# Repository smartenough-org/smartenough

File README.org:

* SmartEnough
SmartEnough is an open source smart home solution that combines affordable
off-the-shelf hardware with a robust software architecture. Built for people
that don't want to pay premium for each IO they add to the system, who want to
trust the system's reliability and who are not afraid of some tinkering.

** SmartEnough design goals
- Extra cheap hardware: doable by hand (soldering iron or breadboard) and
  upgradable to something more sturdy with ordered PCBs. 48+ IO per single board
  possible and way cheaper $/IO than in any available commercial solutions.
- Robust, resiliant, secure: communication and power over twisted pair cables -
  no batteries, no radio, no cloud.
- Supports house wiring in "constellation of star topologies". We don't have a
  device in each light switch or socket, but neither are we limited to a single
  central control point. Cables from lights/shutters and switches should meet
  somewhere in one or more electrical boxes that are connected together with a
  twisted pair cable to form a CAN bus. Bus can span multiple devices in single
  electrical box, or connect multiple points in a bus or semi-bus configuration.
- Instant response to input.
- Event on one board can cause an action on another (eg. stair switches) via a
  bus without requiring a computer and HomeAssistant - eg. stair lighting.
- Can gather door/window/movement sensor data and be used as an alarm system.
- Open & customizable: I'm building it to suit my needs, trying to keep it open
  for any additional sensible functions.
- Integrates with HomeAssistant, but can do a lot without it.

** Resources
The core system software is in two repositories:
- [[https://github.com/smartenough-org/io-ctrl][io-ctrl]]:
  Firmware for IO controller board that handles IO - reads switches and
  sensors, changes outputs. Contains also firmware for hardware part (left side)
  of =CAN<->USB<->MQTT= bridge to talk to HomeAssistant.
- [[https://github.com/smartenough-org/io-gate][io-gate]]:
  computer part of =CAN<->USB<->MQT= bridge (right part) to convert CAN
  messages to MQTT events that can be understood by HomeAssistant.
- Firmware is in Rust, written with Embassy framework for STM32G431 device.
  Should migrate easy enough to other chips assuming enough peripherals are
  available (CAN and USB working together, 128kB+ Flash, 32kB+ RAM).

Rest of the resources include:
- KiCAD (schematic + board) designs for IO controller board (can be used for
  gate as well).
- KiCAD for organized power injection with protection.
- KiCAD for additional ESPHOME boards for less critical components (like
  temperature sensors).
- 3D printing (FreeCad) designs for DIN rail (mount in electrical boxes) and
  other project boxes for boards (OpenSCAD).
- This repository in addition can contain anything smarthome related I might
  publish (eg. some micropython watering experiments)

** Example deployment
[[media/deployment-diagram.png]]

That's my currently working deployment. NOTE: CAN should not be a star, it
should be a bus. Hence in one case I send CAN signal back over another cable
pair in the same cable to "flatten" it out. Bus gets longer (it's around 50m
total), but stubs are shorter.

*** Connecting cables
I use two pairs for power, one for CAN and one for optional CAN return and a bit
weird RJ45 wiring to indicate the cable is a "SMART" cable not Ethernet. I also
mark those in a visible way. Anything will work as long as CAN and FORWARD is in
the same twisted pair (my mapping will work with normal T568B too).

| T568B | CAN  |   |                       |
|-------+------+---+-----------------------|
| w-o   | w-o  | 1 | CAN_L                 |
| o     | o    | 2 | CAN_H                 |
| w-g   | w-g  | 3 | IN POWER, 24V         |
| bl    | g    | 4 | IN POWER, GND (swap!) |
| w-bl  | w-bl | 5 | IN POWER, 24V         |
| g     | bl   | 6 | IN POWER, GND (swap!) |
| w-br  | w-br | 7 | CAN_L FORWARD         |
| br    | br   | 8 | CAN_H FORWARD         |

*** CAN configuration
I use CAN because it's a multi-master bus, no "leader" device on the BUS needs
to poll for data from "following" devices. When input event occurs or output
changes state a board broadcasts a message on the bus. Another board can see
this message and react by changing it's outputs.

Gate is a special device that serves as a bidirectional =CAN<->USB<->MQTT=
bridge. It receives CAN messages, converts them and publishes them on MQTT. It
also subscribes to MQTT topics and if something is published there it sends a
CAN request to for example toggle an Output.

I use 250kbps CAN speed and 11-bit addressing. I opted for a simple CAN protocol
(as opposed to more versatile CANopen). Address relates to a "message" more than
a "sender/receiver" and is used in determining the priority on the bus. Given
that:
- Messages must be properly unique,
- lower values have higher priorities,
- we want at least 64 devices on the bus,
I picked 6 bit for device address and 5 for message type (32 different message
types). Format: =TTTTTAAAAAA (T)ype + (A)ddress=.

Reporting errors, propagating output/input changes, setting output has higher
priority than requesting status, reporting status, time announcements or some
debug ping/pong messages.

Message body consists of up to 8 bytes of data, system typically uses 2-3.
Example: Request output change has 2 bytes: Index of output to change and byte
representing state (Off, On, Toggle). Message address points at the device that
should change output ("destination").

Message "Output changed" has similarly output index and state (Off, On), but
address points to a message source instead. I don't use RTR (remote frames).

Conscise list of used commands (but see message.rs for details):
- ERROR 0x02 - Error happened.
- OUTPUT_CHANGED 0x04 - My output changed
- INPUT_CHANGED 0x05 -  My input was changed
- SET_OUTPUT 0x08 - Set output X to Y (or invert state)
- CALL_PROC 0x0A - Call a predefined procedure in VM
- CALL_SHUTTER 0x0B - Pass command to Shutter code
- STATUS_IO 0x0E - My current IO status, not necessarily changed.
- INFO 0x12 - Similar to ERROR, but low priority (eg. Device started)
- PONG 0x1D
- PING 0x1E

Call Shutter is longest command as it includes a shutter index and a command
byte that can contain a height and a tilt of the shutter.

** IO Controller MainBoard
For details on components and software see
[[https://github.com/smartenough-org/io-ctrl][io-ctrl]].

This board controls IOs when paired with some relay/SSR module. It sits in an
electrical box where it can read signals from light switches and control power
to lighting. It's talks with the world via classical twisted pair cable: CAT5e
UTP. Cable carries power (24V+) and a CAN bus.

[[hardware/board_v1.png]]
[[hardware/schematic_v1.png]]

** Power distribution board
Power board distributes power with some protection (capacitors, resettable
individual fuses, main fuses, zener diodes to limit voltage, diodes to prevent
invalid polarization). It also connects CAN BUS together in configured various
ways (directly, or using FORWARD pair). In general it allows me to connect the
cables from boards in the main central hub easily.

[[hardware/powerboard_v1.png]]

** ESPHome "Uniboard"
It's not strictly part of my main smarthome. A universal PCB board for ESP32 S2
Mini modules I have. It has power stabilization, 1-wire pull-up, some analog
inputs, RS485 interface, four MOSFETs for RGBW or anything else (garage door
control).

I use it with Esphome (over Wifi) where I can't reach with my CAN bus, or where
I don't need the resiliency or just temporarily. For example to gather
temperature readings around heat pump.

[[hardware/uniboard.png]]

** Greenfinger

Automatic plant watering using ESP8266 (or ESP32) using Micropython.
Integrates with HomeAssistant over MQTT:
- Reports status (humidity, operations).
- Can be controlled over MQTT (more water NOW).

It was 100% stable during a period of about a year. Plants died for unrelated
reasons. ;)

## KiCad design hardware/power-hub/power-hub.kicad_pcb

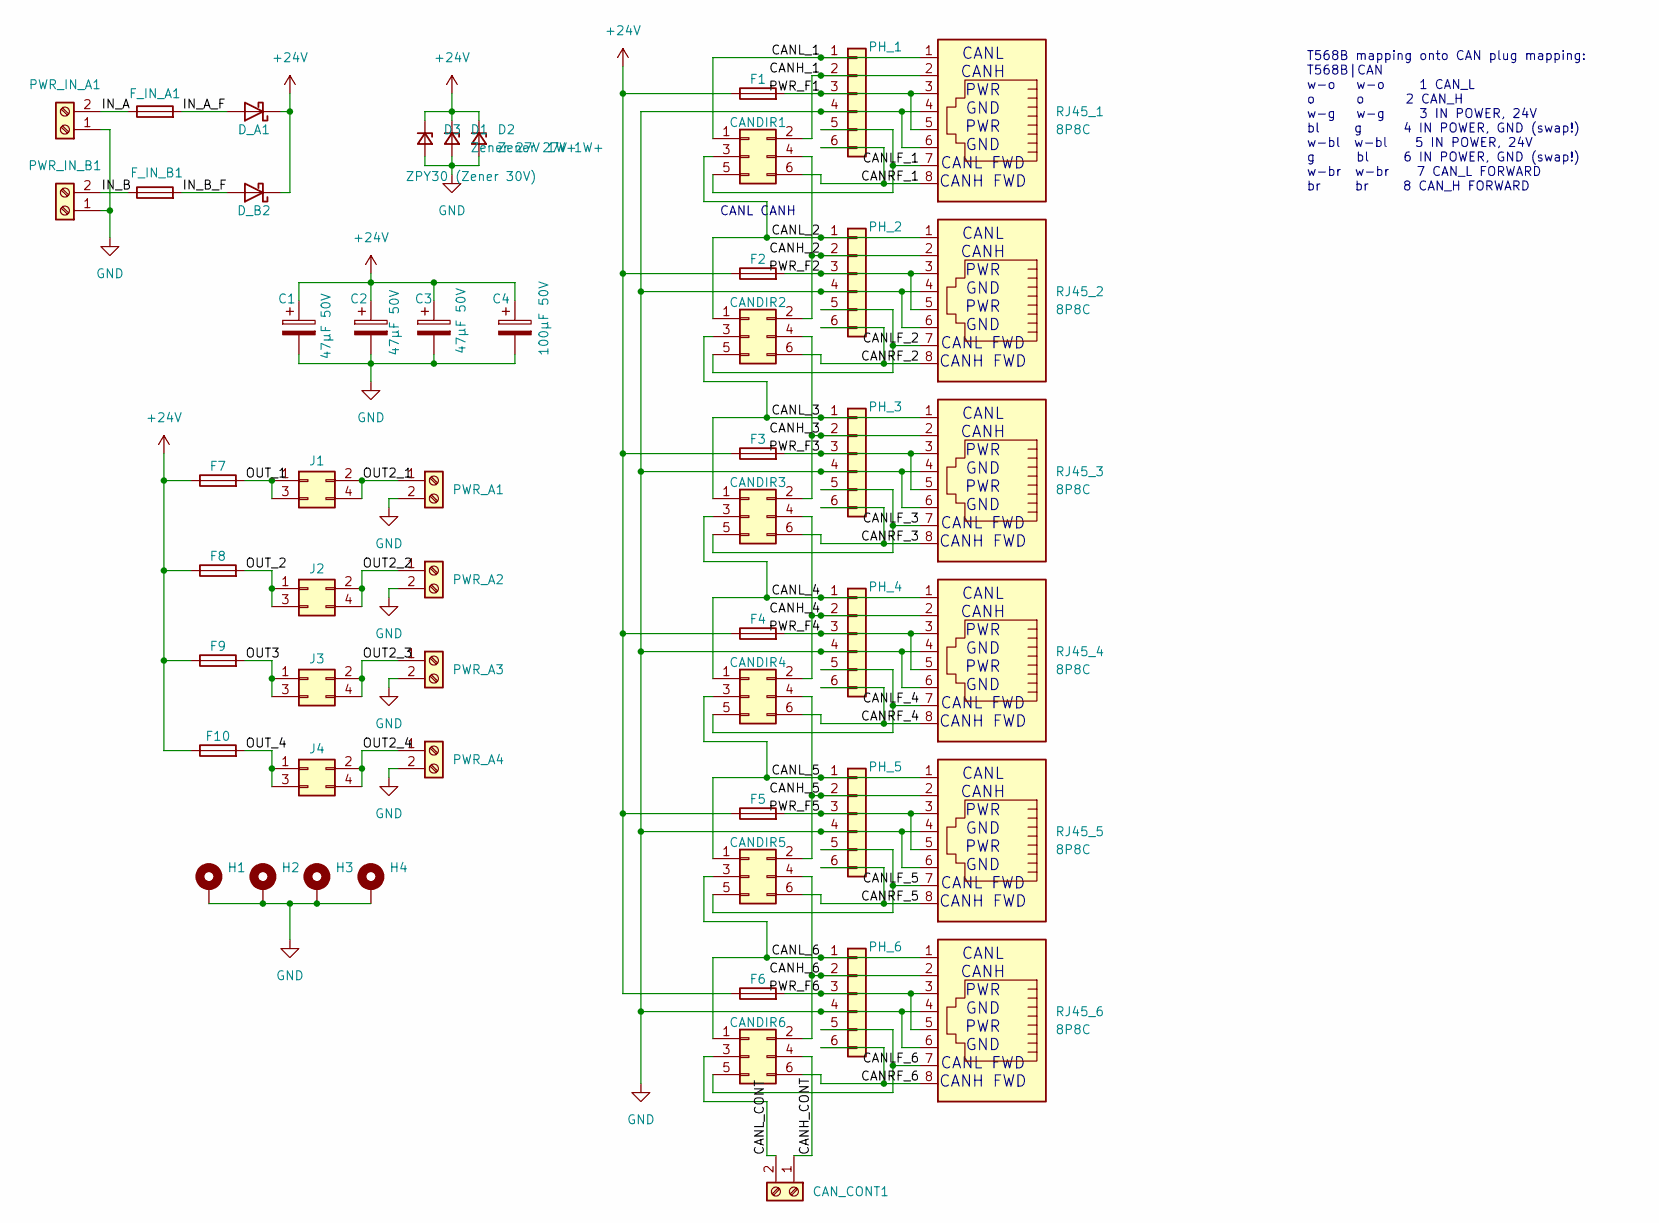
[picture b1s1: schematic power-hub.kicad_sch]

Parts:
C1, C2, C3: 47µF 50V; CP_Radial_D6.3mm_P2.50mm
C4: 100µF 50V; CP_Radial_D8.0mm_P2.50mm
CANDIR1, CANDIR2, CANDIR3, CANDIR4, CANDIR5, CANDIR6: Conn_02x03_Odd_Even; PinHeader_2x03_P2.54mm_Vertical
CAN_CONT1: Screw_Terminal_01x02; TerminalBlock_RND_205-00232_1x02_P5.08mm_Horizontal
D1, D2: Zener 27V 1W+; D_5W_P12.70mm_Horizontal
D3: ZPY30 (Zener 30V); D_5W_P12.70mm_Horizontal
D_A1: 1N5822; D_DO-201AD_P15.24mm_Horizontal
D_B2: 1N5822; D_DO-201AD_P15.24mm_Horizontal
F1, F2, F3, F4, F5, F6, F7, F8, F9, F10: Fuse; Fuse_BelFuse_0ZRE0016FF_L9.9mm_W3.8mm
F_IN_A1: Fuse; Fuseholder_Clip-5x20mm_Keystone_3517_Inline_P23.11x6.76mm_D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
F_IN_B1: Fuse; Fuseholder_Clip-5x20mm_Keystone_3517_Inline_P23.11x6.76mm_D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
H1, H2, H3, H4: MountingHole_Pad; MountingHole_3.2mm_M3_Pad
J1, J2, J3, J4: Conn_02x02_Odd_Even; PinHeader_2x02_P2.54mm_Vertical
PH_1, PH_2, PH_3, PH_4, PH_5, PH_6: Conn_01x06; PinSocket_1x06_P2.54mm_Vertical
PWR_A1, PWR_A2, PWR_A3, PWR_A4: Screw_Terminal_01x02; TerminalBlock_RND_205-00232_1x02_P5.08mm_Horizontal
PWR_IN_A1: Screw_Terminal_01x02; TerminalBlock_RND_205-00232_1x02_P5.08mm_Horizontal
PWR_IN_B1: Screw_Terminal_01x02; TerminalBlock_RND_205-00232_1x02_P5.08mm_Horizontal
RJ45_1, RJ45_2, RJ45_3, RJ45_4, RJ45_5, RJ45_6: 8P8C; RJ45_OST_PJ012-8P8CX_Vertical

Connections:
+24V: C1.1, C2.1, C3.1, C4.1, D1.1 (K), D2.1 (K), D3.1 (K), D_A1.1 (K), D_B2.1 (K), F1.1, F2.1, F3.1, F4.1, F5.1, F6.1, F7.1, F8.1, F9.1, F10.1
/CANH_1: CANDIR1.2, PH_1.2, RJ45_1.2
/CANH_2: CANDIR1.4, CANDIR2.2, PH_2.2, RJ45_2.2
/CANH_3: CANDIR2.4, CANDIR3.2, PH_3.2, RJ45_3.2
/CANH_4: CANDIR3.4, CANDIR4.2, PH_4.2, RJ45_4.2
/CANH_5: CANDIR4.4, CANDIR5.2, PH_5.2, RJ45_5.2
/CANH_6: CANDIR5.4, CANDIR6.2, PH_6.2, RJ45_6.2
/CANH_CONT: CANDIR6.4, CAN_CONT1.1
/CANLF_1: CANDIR1.5, PH_1.5, RJ45_1.7
/CANLF_2: CANDIR2.5, PH_2.5, RJ45_2.7
/CANLF_3: CANDIR3.5, PH_3.5, RJ45_3.7
/CANLF_4: CANDIR4.5, PH_4.5, RJ45_4.7
/CANLF_5: CANDIR5.5, PH_5.5, RJ45_5.7
/CANLF_6: CANDIR6.5, PH_6.5, RJ45_6.7
/CANL_1: CANDIR1.1, PH_1.1, RJ45_1.1
/CANL_2: CANDIR1.3, CANDIR2.1, PH_2.1, RJ45_2.1
/CANL_3: CANDIR2.3, CANDIR3.1, PH_3.1, RJ45_3.1
/CANL_4: CANDIR3.3, CANDIR4.1, PH_4.1, RJ45_4.1
/CANL_5: CANDIR4.3, CANDIR5.1, PH_5.1, RJ45_5.1
/CANL_6: CANDIR5.3, CANDIR6.1, PH_6.1, RJ45_6.1
/CANL_CONT: CANDIR6.3, CAN_CONT1.2
/CANRF_1: CANDIR1.6, PH_1.6, RJ45_1.8
/CANRF_2: CANDIR2.6, PH_2.6, RJ45_2.8
/CANRF_3: CANDIR3.6, PH_3.6, RJ45_3.8
/CANRF_4: CANDIR4.6, PH_4.6, RJ45_4.8
/CANRF_5: CANDIR5.6, PH_5.6, RJ45_5.8
/CANRF_6: CANDIR6.6, PH_6.6, RJ45_6.8
/IN_A: F_IN_A1.1, PWR_IN_A1.2
/IN_A_F: D_A1.2 (A), F_IN_A1.2
/IN_B: F_IN_B1.1, PWR_IN_B1.2
/IN_B_F: D_B2.2 (A), F_IN_B1.2
/OUT2_1: J1.2, J1.4, PWR_A1.1
/OUT2_2: J2.2, J2.4, PWR_A2.1
/OUT2_3: J3.2, J3.4, PWR_A3.1
/OUT2_4: J4.2, J4.4, PWR_A4.1
/OUT3: F9.2, J3.1, J3.3
/OUT_1: F7.2, J1.1, J1.3
/OUT_2: F8.2, J2.1, J2.3
/OUT_4: F10.2, J4.1, J4.3
/PWR_F1: F1.2, PH_1.3, RJ45_1.3, RJ45_1.5
/PWR_F2: F2.2, PH_2.3, RJ45_2.3, RJ45_2.5
/PWR_F3: F3.2, PH_3.3, RJ45_3.3, RJ45_3.5
/PWR_F4: F4.2, PH_4.3, RJ45_4.3, RJ45_4.5
/PWR_F5: F5.2, PH_5.3, RJ45_5.3, RJ45_5.5
/PWR_F6: F6.2, PH_6.3, RJ45_6.3, RJ45_6.5
GND: C1.2, C2.2, C3.2, C4.2, D1.2 (A), D2.2 (A), D3.2 (A), H1.1, H2.1, H3.1, H4.1, PH_1.4, PH_2.4, PH_3.4, PH_4.4, PH_5.4, PH_6.4, PWR_A1.2, PWR_A2.2, PWR_A3.2, PWR_A4.2, PWR_IN_A1.1, PWR_IN_B1.1, RJ45_1.4, RJ45_1.6, RJ45_2.4, RJ45_2.6, RJ45_3.4, RJ45_3.6, RJ45_4.4, RJ45_4.6, RJ45_5.4, RJ45_5.6, RJ45_6.4, RJ45_6.6

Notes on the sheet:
CANL CANH PWR GND PWR GND CANL FWD CANH FWD
T568B mapping onto CAN plug mapping: T568B|CAN w-o w-o 1 CAN_L o o 2 CAN_H w-g w-g 3 IN POWER, 24V bl g 4 IN POWER, GND (swap!) w-bl w-bl 5 IN POWER, 24V g bl 6 IN POWER, GND (swap!) w-br w-br 7 CAN_L FORWARD br br 8 CAN_H FORWARD
CANL CANH

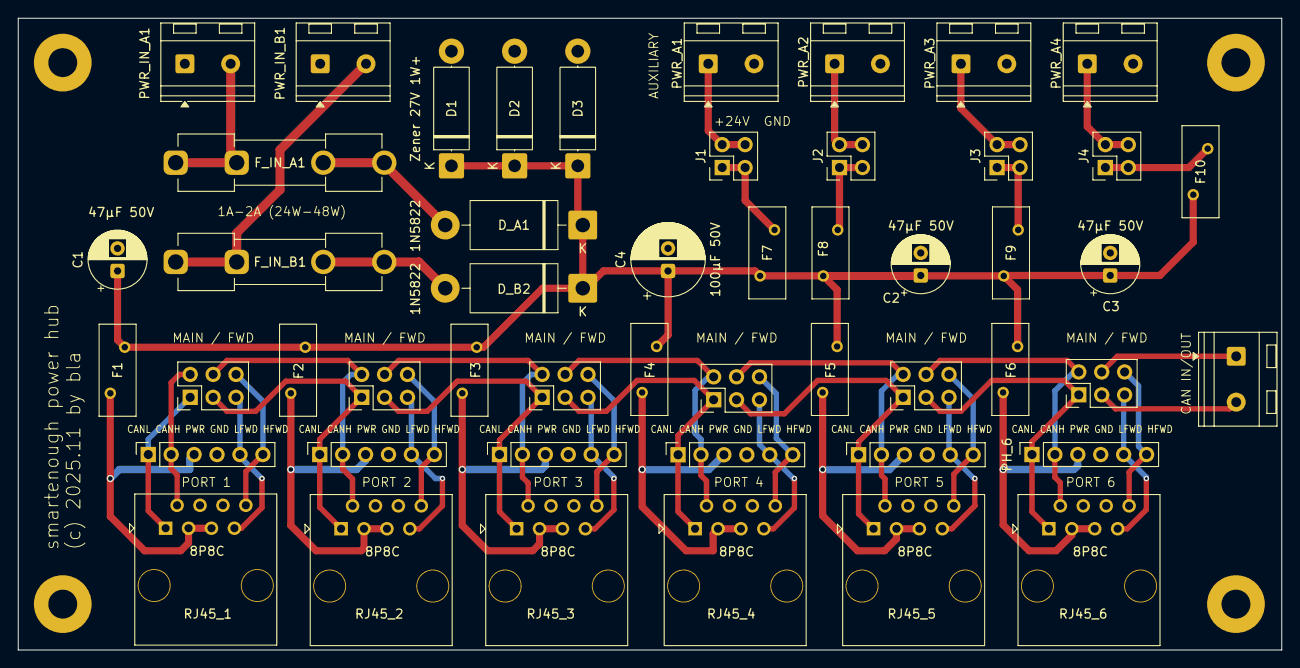
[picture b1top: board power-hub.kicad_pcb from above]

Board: 2 copper layers, 140.0 x 70.0 mm, 54 parts (0 on the bottom side), 46 nets.

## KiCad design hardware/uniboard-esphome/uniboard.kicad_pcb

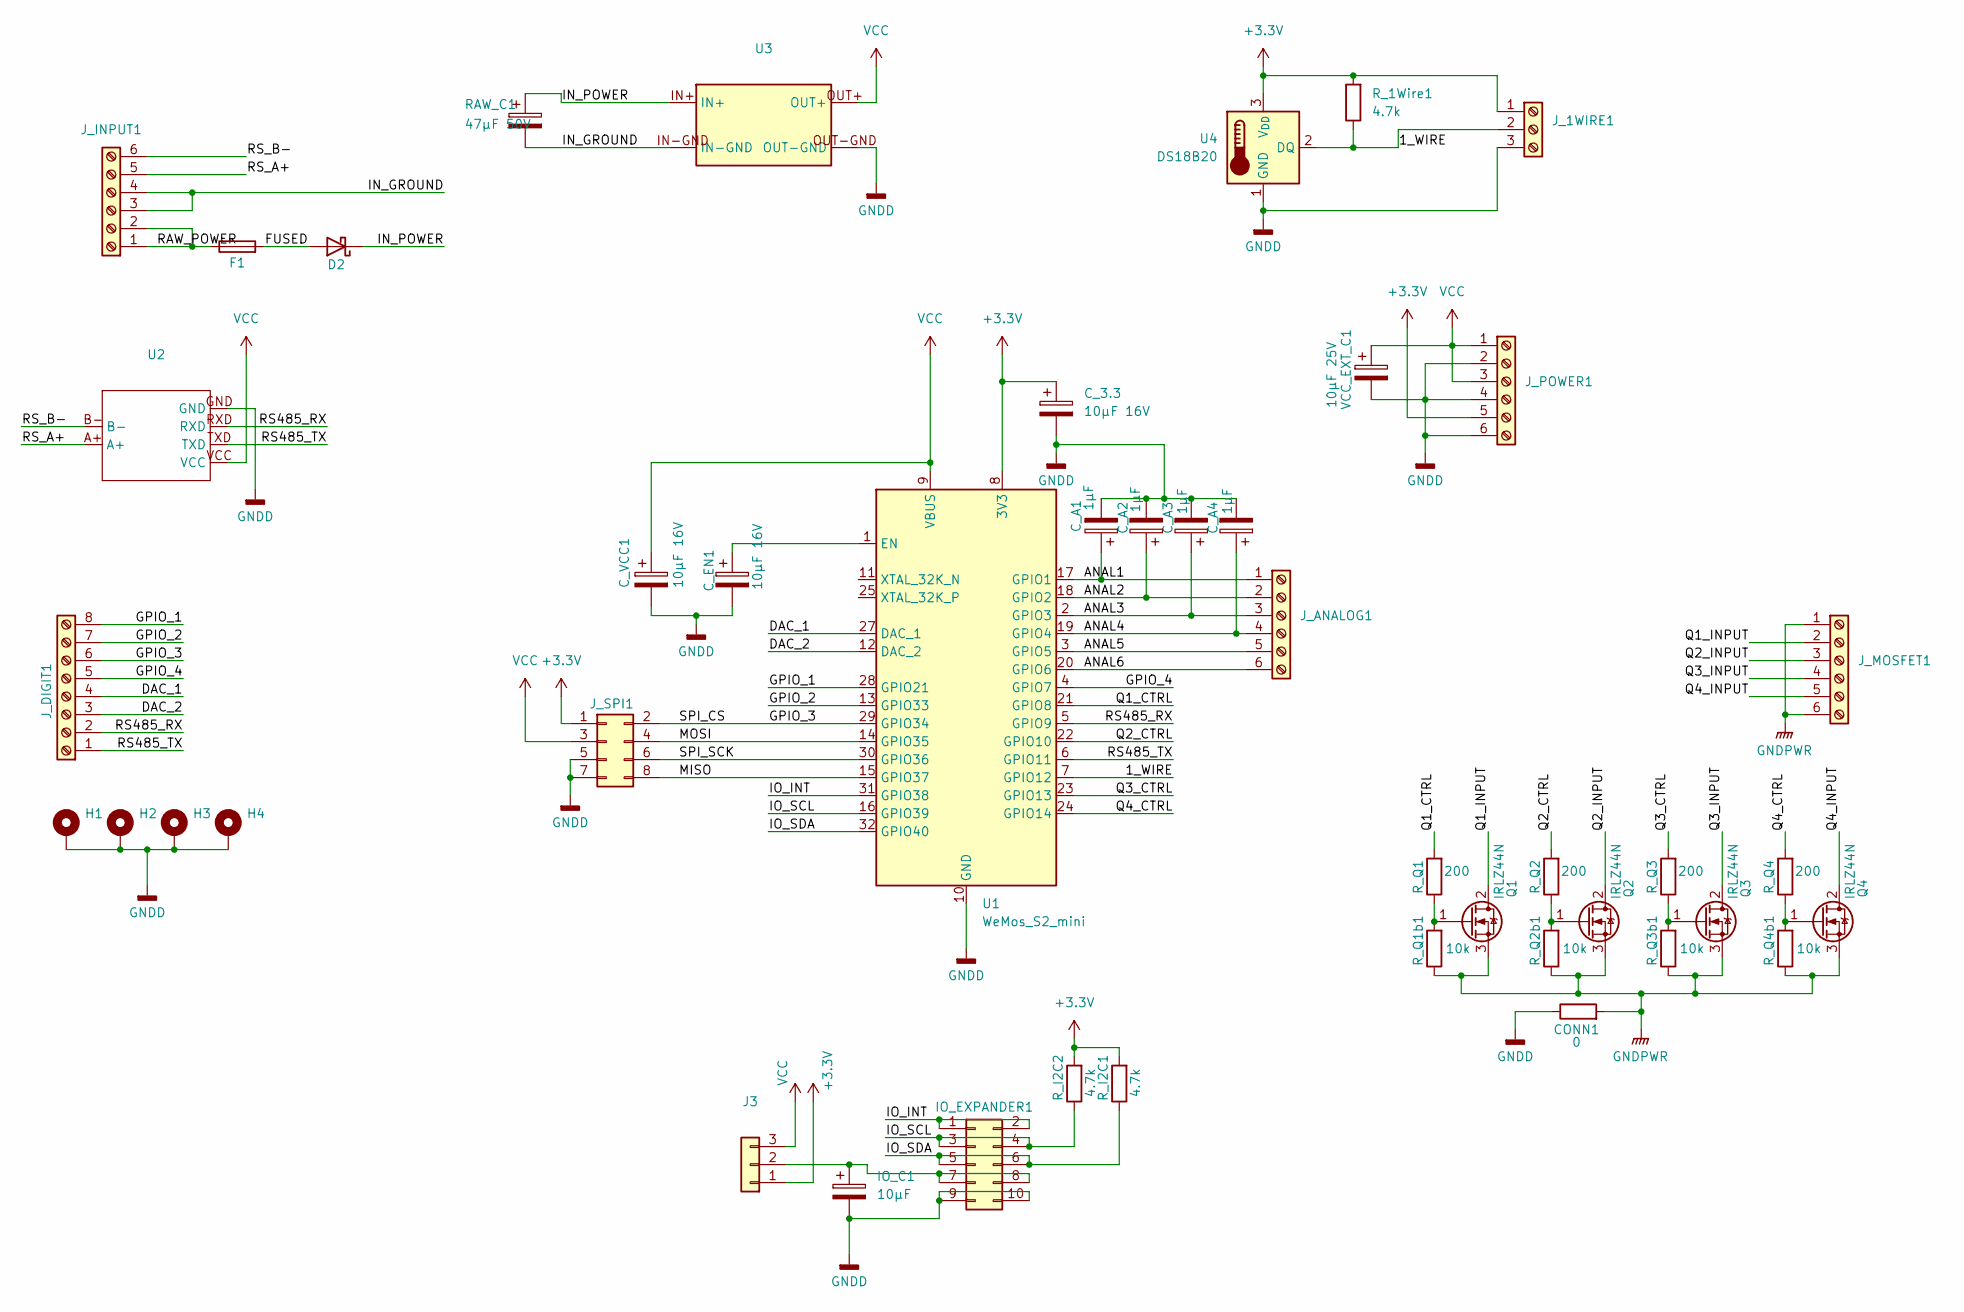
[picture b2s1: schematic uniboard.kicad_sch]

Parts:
CONN1: 0; R_0508_1220Metric
C_3.3: 10µF 16V; CP_Radial_D4.0mm_P2.00mm
C_A1, C_A2, C_A3, C_A4: 1µF; CP_Radial_D4.0mm_P2.00mm
C_EN1: 10µF 16V; CP_Radial_D4.0mm_P2.00mm
C_VCC1: 10µF 16V; CP_Radial_D4.0mm_P2.00mm
D2: 1N5822; D_DO-201AD_P15.24mm_Horizontal
F1: Fuse; Fuse_BelFuse_0ZRE0100FF_L18.7mm_W5.1mm
H1, H2, H3, H4: MountingHole_Pad; MountingHole_3.2mm_M3_Pad
IO_C1: 10µF; CP_Radial_D6.3mm_P2.50mm
IO_EXPANDER1: Conn_02x05_Odd_Even; PinSocket_2x05_P2.54mm_Vertical
J3: Conn_01x03; PinHeader_1x03_P2.54mm_Vertical
J_1WIRE1: Screw_Terminal_01x03; TerminalBlock_RND_205-00233_1x03_P5.08mm_Horizontal
J_ANALOG1: Screw_Terminal_01x06; TerminalBlock_RND_205-00236_1x06_P5.08mm_Horizontal
J_DIGIT1: Screw_Terminal_01x08; TerminalBlock_RND_205-00238_1x08_P5.08mm_Horizontal
J_INPUT1: Screw_Terminal_01x06; TerminalBlock_RND_205-00236_1x06_P5.08mm_Horizontal
J_MOSFET1: Screw_Terminal_01x06; TerminalBlock_RND_205-00236_1x06_P5.08mm_Horizontal
J_POWER1: Screw_Terminal_01x06; TerminalBlock_RND_205-00236_1x06_P5.08mm_Horizontal
J_SPI1: Conn_02x04_Odd_Even; PinHeader_2x04_P2.54mm_Vertical
Q1, Q2, Q3, Q4: IRLZ44N; TO-220-3_Vertical
RAW_C1: 47µF 50V; CP_Radial_D6.3mm_P2.50mm
R_1Wire1: 4.7k; R_Axial_DIN0207_L6.3mm_D2.5mm_P7.62mm_Horizontal
R_I2C1, R_I2C2: 4.7k; R_Axial_DIN0207_L6.3mm_D2.5mm_P7.62mm_Horizontal
R_Q1, R_Q2, R_Q3, R_Q4: 200; R_Axial_DIN0207_L6.3mm_D2.5mm_P7.62mm_Horizontal
R_Q1b1, R_Q2b1, R_Q3b1, R_Q4b1: 10k; R_Axial_DIN0207_L6.3mm_D2.5mm_P7.62mm_Horizontal
U1: WeMos_S2_mini; WEMOS_S2_mini
U2: mod_hw-0519-rs-485
U3: mod_LM2596
U4: DS18B20; TO-92_Inline
VCC_EXT_C1: 10µF 25V; CP_Radial_D4.0mm_P2.00mm

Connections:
+3.3V: C_3.3.1, J3.1, J_1WIRE1.1, J_POWER1.5, J_SPI1.1, R_1Wire1.2, R_I2C1.2, R_I2C2.2, U1.8 (3V3), U4.3 (V_{DD})
/1_WIRE: J_1WIRE1.2, R_1Wire1.1, U1.7 (GPIO12), U4.2 (DQ)
/ANAL1: C_A1.1, J_ANALOG1.1, U1.17 (GPIO1)
/ANAL2: C_A2.1, J_ANALOG1.2, U1.18 (GPIO2)
/ANAL3: C_A3.1, J_ANALOG1.3, U1.2 (GPIO3)
/ANAL4: C_A4.1, J_ANALOG1.4, U1.19 (GPIO4)
/ANAL5: J_ANALOG1.5, U1.3 (GPIO5)
/ANAL6: J_ANALOG1.6, U1.20 (GPIO6)
/DAC_1: J_DIGIT1.4, U1.27 (DAC_1)
/DAC_2: J_DIGIT1.3, U1.12 (DAC_2)
/FUSED: D2.2 (A), F1.2
/GPIO_1: J_DIGIT1.8, U1.28 (GPIO21)
/GPIO_2: J_DIGIT1.7, U1.13 (GPIO33)
/GPIO_3: J_DIGIT1.6, J_SPI1.2, U1.29 (GPIO34)
/GPIO_4: J_DIGIT1.5, U1.4 (GPIO7)
/IN_GROUND: J_INPUT1.3, J_INPUT1.4, RAW_C1.2, U3.IN-GND
/IN_POWER: D2.1 (K), RAW_C1.1, U3.IN+
/IO_INT: IO_EXPANDER1.1, IO_EXPANDER1.2, U1.31 (GPIO38)
/IO_SCL: IO_EXPANDER1.3, IO_EXPANDER1.4, R_I2C2.1, U1.16 (GPIO39)
/IO_SDA: IO_EXPANDER1.5, IO_EXPANDER1.6, R_I2C1.1, U1.32 (GPIO40)
/MISO: J_SPI1.8, U1.15 (GPIO37)
/MOSI: J_SPI1.4, U1.14 (GPIO35)
/Q1_CTRL: R_Q1.2, U1.21 (GPIO8)
/Q1_INPUT: J_MOSFET1.2, Q1.2 (D)
/Q2_CTRL: R_Q2.2, U1.22 (GPIO10)
/Q2_INPUT: J_MOSFET1.3, Q2.2 (D)
/Q3_CTRL: R_Q3.2, U1.23 (GPIO13)
/Q3_INPUT: J_MOSFET1.4, Q3.2 (D)
/Q4_CTRL: R_Q4.2, U1.24 (GPIO14)
/Q4_INPUT: J_MOSFET1.5, Q4.2 (D)
/RAW_POWER: F1.1, J_INPUT1.1, J_INPUT1.2
/RS485_RX: J_DIGIT1.2, U1.5 (GPIO9), U2.RXD
/RS485_TX: J_DIGIT1.1, U1.6 (GPIO11), U2.TXD
/RS_A+: J_INPUT1.5, U2.A+
/RS_B-: J_INPUT1.6, U2.B-
/SPI_SCK: J_SPI1.6, U1.30 (GPIO36)
GNDD: CONN1.1, C_3.3.2, C_A1.2, C_A2.2, C_A3.2, C_A4.2, C_EN1.2, C_VCC1.2, H1.1, H2.1, H3.1, H4.1, IO_C1.2, IO_EXPANDER1.9, IO_EXPANDER1.10, J_1WIRE1.3, J_POWER1.2, J_POWER1.4, J_POWER1.6, J_SPI1.5, J_SPI1.7, U1.10 (GND), U1.26 (GND), U2.GND, U3.OUT-GND, U4.1 (GND), VCC_EXT_C1.2
GNDPWR: CONN1.2, J_MOSFET1.1, J_MOSFET1.6, Q1.3 (S), Q2.3 (S), Q3.3 (S), Q4.3 (S), R_Q1b1.1, R_Q2b1.1, R_Q3b1.1, R_Q4b1.1
unnamed: IO_C1.1, IO_EXPANDER1.7, IO_EXPANDER1.8, J3.2
unnamed: Q1.1 (G), R_Q1.1, R_Q1b1.2
unnamed: Q2.1 (G), R_Q2.1, R_Q2b1.2
unnamed: Q3.1 (G), R_Q3.1, R_Q3b1.2
unnamed: Q4.1 (G), R_Q4.1, R_Q4b1.2
unnamed: C_EN1.1, U1.1 (EN)
VCC: C_VCC1.1, J3.3, J_POWER1.1, J_POWER1.3, J_SPI1.3, U1.9 (VBUS), U2.VCC, U3.OUT+, VCC_EXT_C1.1

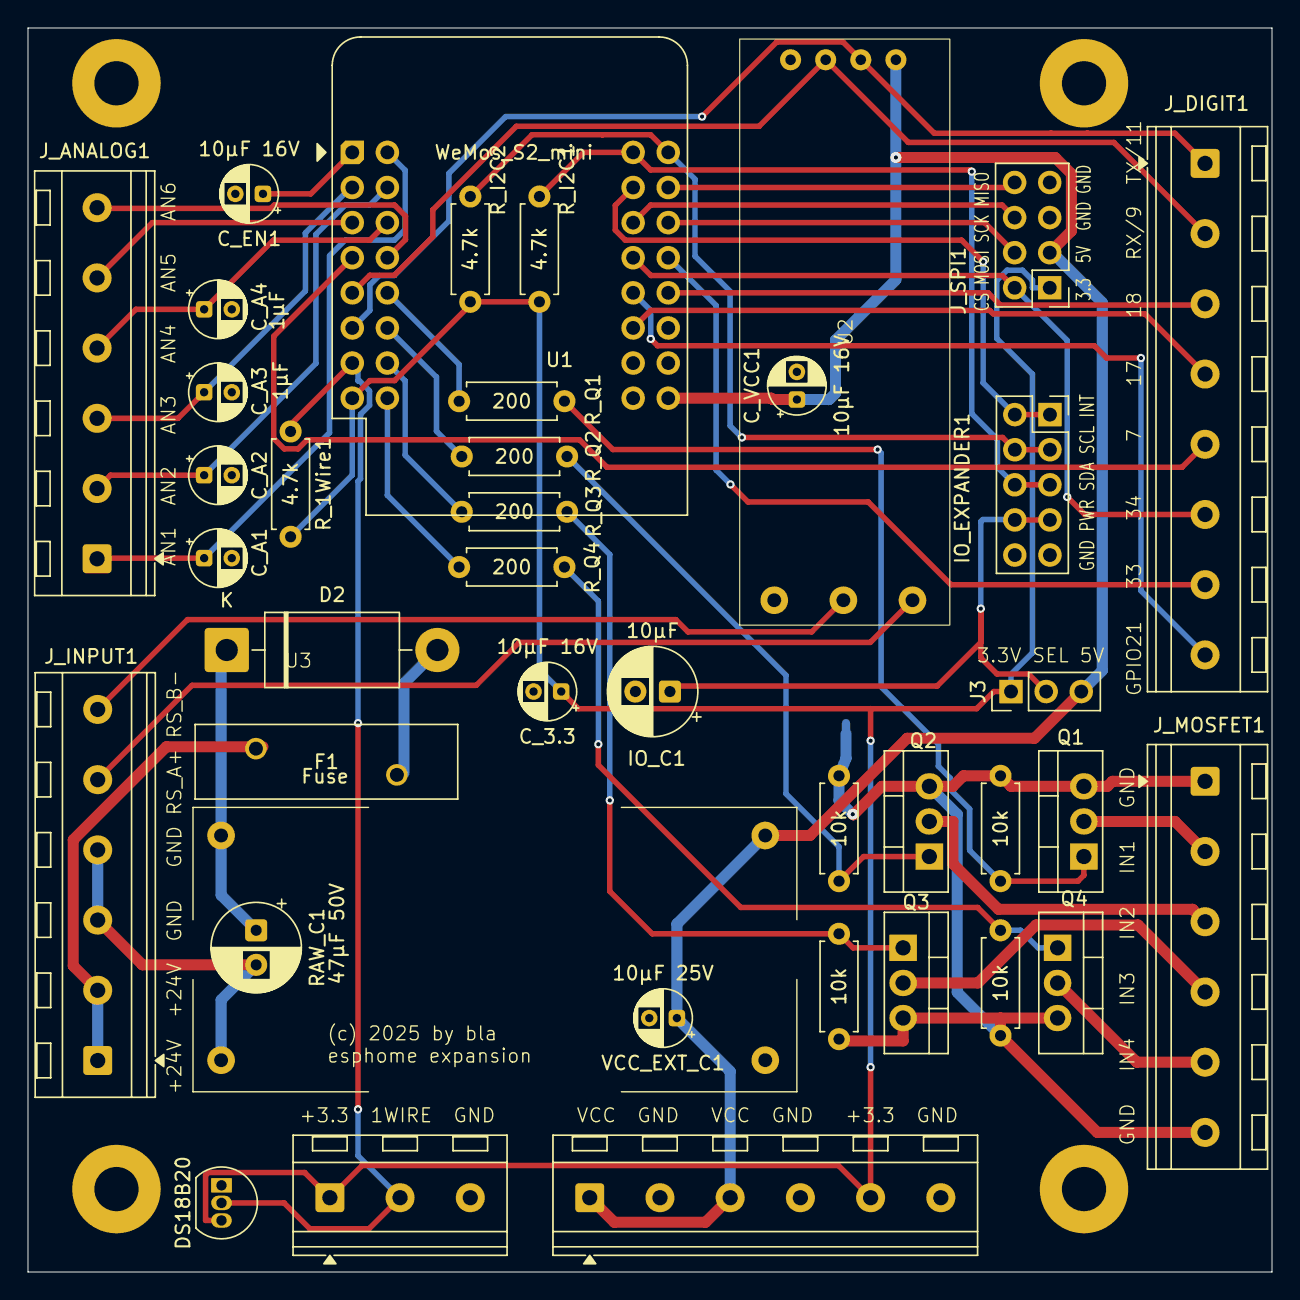
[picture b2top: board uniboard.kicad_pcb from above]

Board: 2 copper layers, 90.0 x 90.0 mm, 45 parts (1 on the bottom side), 45 nets.

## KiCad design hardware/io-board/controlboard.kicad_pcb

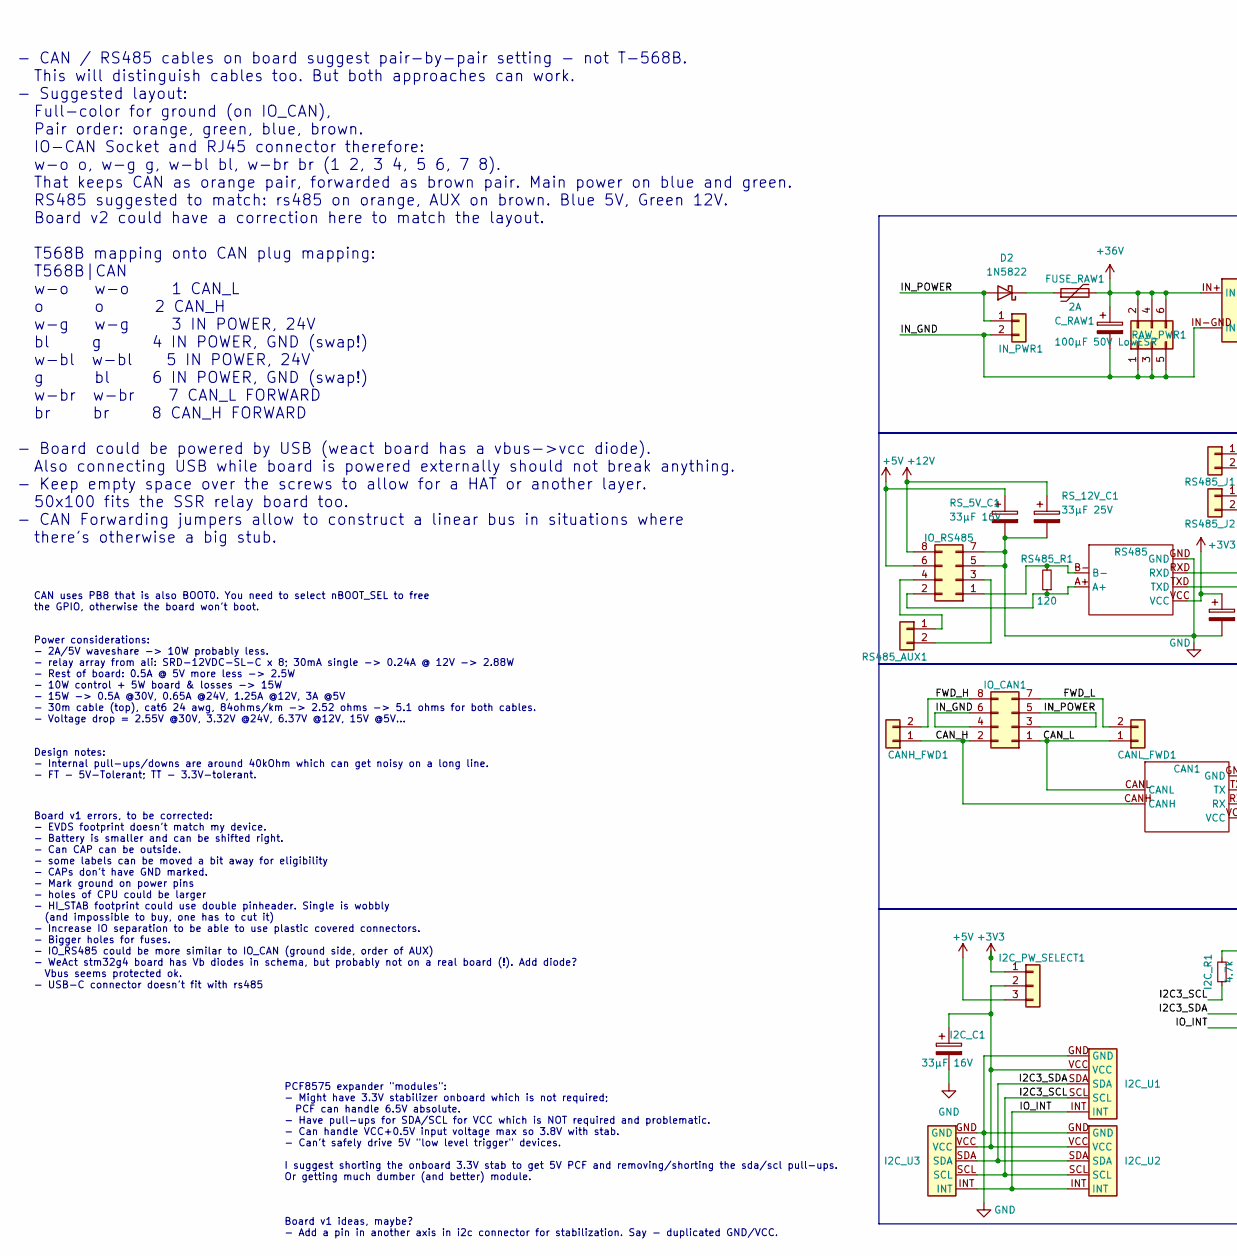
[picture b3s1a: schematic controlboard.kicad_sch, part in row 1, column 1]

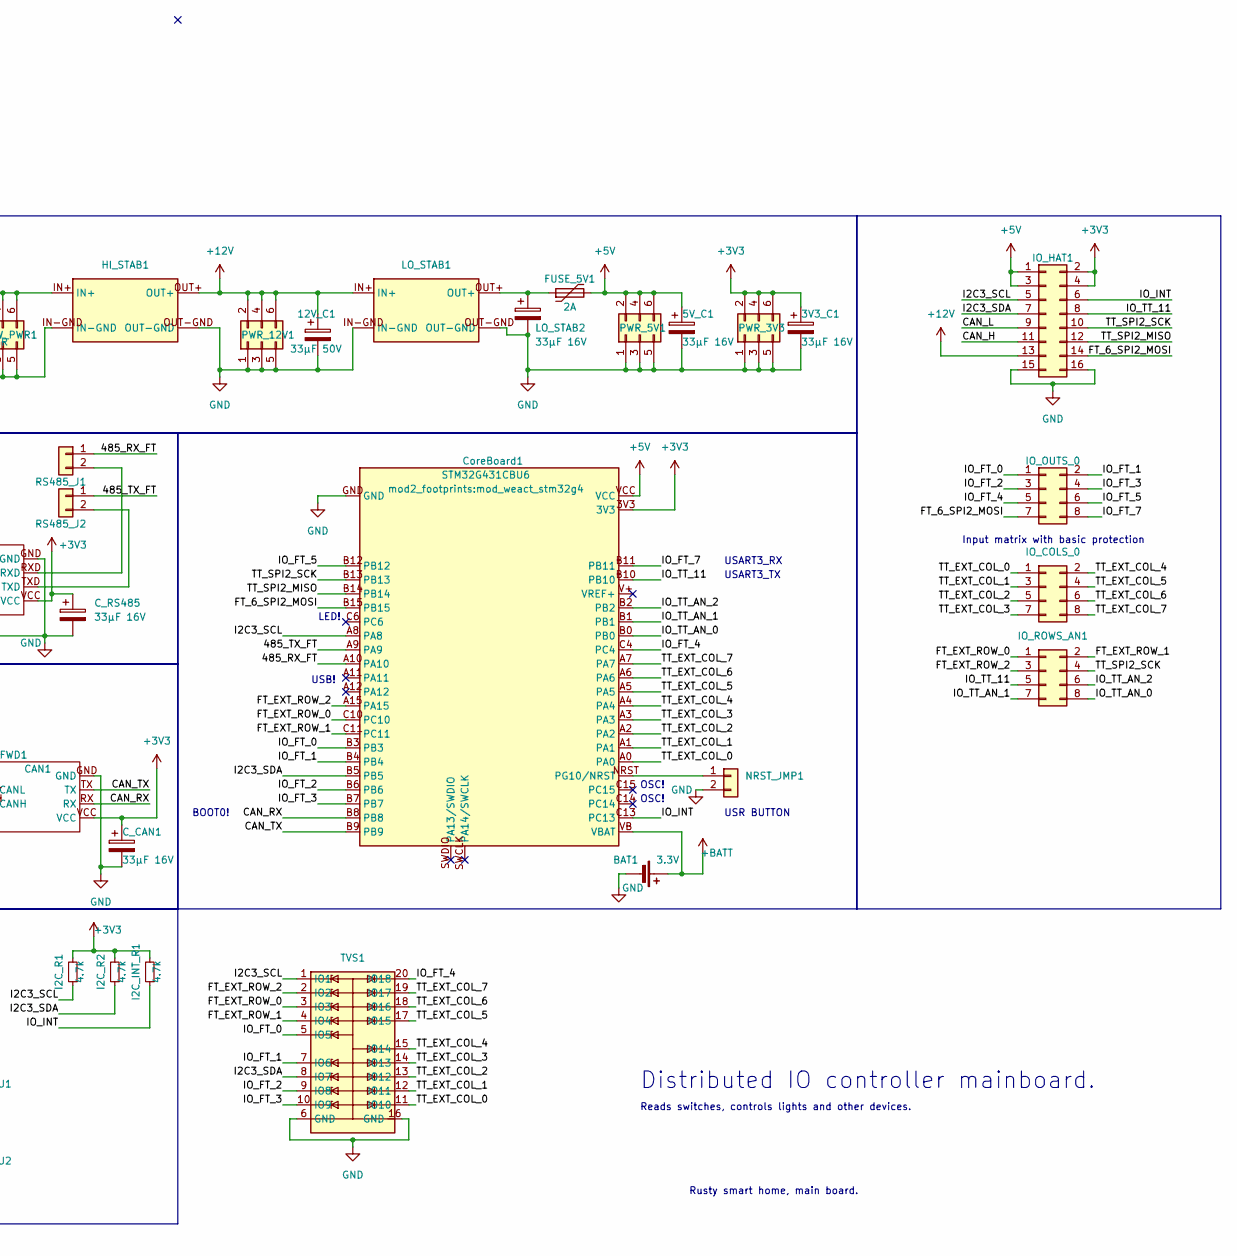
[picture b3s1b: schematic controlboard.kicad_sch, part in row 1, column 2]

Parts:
3V3_C1, 5V_C1: 33µF 16V; C_Radial_D4.0mm_H7.0mm_P1.50mm
12V_C1: 33µF 50V; C_Radial_D5.0mm_H7.0mm_P2.00mm
BAT1: 3.3V; BatteryHolder_ComfortableElectronic_CH273-2450_1x2450
CAN1: mod_tja1050_can
CANH_FWD1: Conn_01x02; PinHeader_1x02_P2.54mm_Vertical
CANL_FWD1: Conn_01x02; PinHeader_1x02_P2.54mm_Vertical
C_CAN1: 33µF 16V; C_Radial_D4.0mm_H7.0mm_P1.50mm
C_RAW1: 100µF 50V LowESR; C_Radial_D10.0mm_H12.5mm_P5.00mm
C_RS485: 33µF 16V; C_Radial_D4.0mm_H7.0mm_P1.50mm
CoreBoard1: STM32G431CBU6; mod_weact_stm32g4
D2: 1N5822; D_DO-201AD_P15.24mm_Horizontal
FUSE_5V1: 2A; Fuse_BelFuse_0ZRE0016FF_L9.9mm_W3.8mm
FUSE_RAW1: 2A; Fuse_BelFuse_0ZRE0016FF_L9.9mm_W3.8mm
HI_STAB1: mod_LM2596
I2C_C1: 33µF 16V; C_Radial_D4.0mm_H7.0mm_P1.50mm
I2C_INT_R1, I2C_R1, I2C_R2: 4.7k; R_0805_2012Metric_Pad1.20x1.40mm_HandSolder
I2C_PW_SELECT1: Conn_01x03; PinHeader_1x03_P2.54mm_Vertical
I2C_U1, I2C_U2, I2C_U3: mod_pcf8575_16bit_vertical
IN_PWR1: Conn_01x02; PinHeader_1x02_P2.54mm_Vertical
IO_CAN1: Conn_02x04_Odd_Even; PinHeader_2x04_P2.54mm_Vertical
IO_COLS_0: Conn_02x04_Odd_Even; PinHeader_2x04_P2.54mm_Vertical
IO_HAT1: Conn_02x08_Odd_Even; PinHeader_2x08_P2.54mm_Vertical
IO_OUTS_0: Conn_02x04_Odd_Even; PinHeader_2x04_P2.54mm_Vertical
IO_ROWS_AN1: Conn_02x04_Odd_Even; PinHeader_2x04_P2.54mm_Vertical
IO_RS485: Conn_02x04_Odd_Even; PinHeader_2x04_P2.54mm_Vertical
LO_STAB1: mod_mp1584_stab
LO_STAB2: 33µF 16V; C_Radial_D5.0mm_H7.0mm_P2.00mm
NRST_JMP1: Conn_01x02; PinHeader_1x02_P2.54mm_Vertical
PWR_3V3, PWR_5V1, PWR_12V1: Conn_02x03_Odd_Even; PinHeader_2x03_P2.54mm_Vertical
RAW_PWR1: Conn_02x03_Odd_Even; PinHeader_2x03_P2.54mm_Vertical
RS485: mod_hw-0519-rs-485
RS485_AUX1, RS485_J1, RS485_J2: Conn_01x02; PinHeader_1x02_P2.54mm_Vertical
RS485_R1: 120; R_0805_2012Metric_Pad1.20x1.40mm_HandSolder
RS_5V_C1: 33µF 16V; C_Radial_D4.0mm_H7.0mm_P1.50mm
RS_12V_C1: 33µF 25V; C_Radial_D4.0mm_H7.0mm_P1.50mm
TVS1: SO-20_5.3x12.6mm_P1.27mm

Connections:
+3V3: 3V3_C1.1, CAN1.VCC, C_CAN1.1, C_RS485.1, CoreBoard1.3V3, I2C_INT_R1.2, I2C_PW_SELECT1.1, I2C_R1.2, I2C_R2.2, IO_HAT1.2, IO_HAT1.4, PWR_3V3.2, PWR_3V3.4, PWR_3V3.6, RS485.VCC
+5V: 5V_C1.1, CoreBoard1.VCC, FUSE_5V1.2, I2C_PW_SELECT1.3, IO_HAT1.1, IO_HAT1.3, IO_RS485.6, PWR_5V1.2, PWR_5V1.4, PWR_5V1.6, RS_5V_C1.1
+12V: 12V_C1.1, HI_STAB1.OUT+, IO_HAT1.13, IO_RS485.8, LO_STAB1.IN+, PWR_12V1.2, PWR_12V1.4, PWR_12V1.6, RS_12V_C1.1
+36V: C_RAW1.1, FUSE_RAW1.2, HI_STAB1.IN+, RAW_PWR1.2, RAW_PWR1.4, RAW_PWR1.6
+BATT: BAT1.1 (+), CoreBoard1.VB (VBAT)
/485_RX_FT: CoreBoard1.A10, RS485_J1.1
/485_TX_FT: CoreBoard1.A9, RS485_J2.1
/CAN_H: CAN1.CANH, CANH_FWD1.1, IO_CAN1.2, IO_HAT1.11
/CAN_L: CAN1.CANL, CANL_FWD1.1, IO_CAN1.1, IO_HAT1.9
/CAN_RX: CAN1.RX, CoreBoard1.B8
/CAN_TX: CAN1.TX, CoreBoard1.B9
/FT_6_SPI2_MOSI: CoreBoard1.B15, IO_HAT1.14, IO_OUTS_0.7
/FT_EXT_ROW_0: CoreBoard1.C10, IO_ROWS_AN1.1, TVS1.3 (IO3)
/FT_EXT_ROW_1: CoreBoard1.C11, IO_ROWS_AN1.2, TVS1.4 (IO4)
/FT_EXT_ROW_2: CoreBoard1.A15, IO_ROWS_AN1.3, TVS1.2 (IO2)
/I2C3_SCL: CoreBoard1.A8, I2C_R1.1, I2C_U1.SCL, I2C_U2.SCL, I2C_U3.SCL, IO_HAT1.5, TVS1.1 (IO1)
/I2C3_SDA: CoreBoard1.B5, I2C_R2.1, I2C_U1.SDA, I2C_U2.SDA, I2C_U3.SDA, IO_HAT1.7, TVS1.8 (IO7)
/IN_GND: C_RAW1.2, HI_STAB1.IN-GND, IN_PWR1.2, IO_CAN1.4, IO_CAN1.6, RAW_PWR1.1, RAW_PWR1.3, RAW_PWR1.5
/IN_POWER: D2.2 (A), IN_PWR1.1, IO_CAN1.3, IO_CAN1.5
/IO_FT_0: CoreBoard1.B3, IO_OUTS_0.1, TVS1.5 (IO5)
/IO_FT_1: CoreBoard1.B4, IO_OUTS_0.2, TVS1.7 (IO6)
/IO_FT_2: CoreBoard1.B6, IO_OUTS_0.3, TVS1.9 (IO8)
/IO_FT_3: CoreBoard1.B7, IO_OUTS_0.4, TVS1.10 (IO9)
/IO_FT_4: CoreBoard1.C4, IO_OUTS_0.5, TVS1.20 (IO18)
/IO_FT_5: CoreBoard1.B12, IO_OUTS_0.6
/IO_FT_7: CoreBoard1.B11, IO_OUTS_0.8
/IO_INT: CoreBoard1.C13, I2C_INT_R1.1, I2C_U1.INT, I2C_U2.INT, I2C_U3.INT, IO_HAT1.6
/IO_TT_11: CoreBoard1.B10, IO_HAT1.8, IO_ROWS_AN1.5
/IO_TT_AN_0: CoreBoard1.B0, IO_ROWS_AN1.8
/IO_TT_AN_1: CoreBoard1.B1, IO_ROWS_AN1.7
/IO_TT_AN_2: CoreBoard1.B2, IO_ROWS_AN1.6
/TT_EXT_COL_0: CoreBoard1.A0, IO_COLS_0.1, TVS1.11 (IO10)
/TT_EXT_COL_1: CoreBoard1.A1, IO_COLS_0.3, TVS1.12 (IO11)
/TT_EXT_COL_2: CoreBoard1.A2, IO_COLS_0.5, TVS1.13 (IO12)
/TT_EXT_COL_3: CoreBoard1.A3, IO_COLS_0.7, TVS1.14 (IO13)
/TT_EXT_COL_4: CoreBoard1.A4, IO_COLS_0.2, TVS1.15 (IO14)
/TT_EXT_COL_5: CoreBoard1.A5, IO_COLS_0.4, TVS1.17 (IO15)
/TT_EXT_COL_6: CoreBoard1.A6, IO_COLS_0.6, TVS1.18 (IO16)
/TT_EXT_COL_7: CoreBoard1.A7, IO_COLS_0.8, TVS1.19 (IO17)
/TT_SPI2_MISO: CoreBoard1.B14, IO_HAT1.12
/TT_SPI2_SCK: CoreBoard1.B13, IO_HAT1.10, IO_ROWS_AN1.4
GND: 3V3_C1.2, 5V_C1.2, 12V_C1.2, BAT1.2 (-), CAN1.GND, C_CAN1.2, C_RS485.2, CoreBoard1.GND, HI_STAB1.OUT-GND, I2C_C1.2, I2C_U1.GND, I2C_U2.GND, I2C_U3.GND, IO_HAT1.15, IO_HAT1.16, IO_RS485.5, IO_RS485.7, LO_STAB1.IN-GND, LO_STAB1.OUT-GND, LO_STAB2.2, NRST_JMP1.2, PWR_3V3.1, PWR_3V3.3, PWR_3V3.5, PWR_5V1.1, PWR_5V1.3, PWR_5V1.5, PWR_12V1.1, PWR_12V1.3, PWR_12V1.5, RS485.GND, RS_5V_C1.2, RS_12V_C1.2, TVS1.6 (GND), TVS1.16 (GND); also elsewhere on the board
unnamed: CANH_FWD1.2, IO_CAN1.8
unnamed: CANL_FWD1.2, IO_CAN1.7
unnamed: CoreBoard1.NRST (PG10/NRST), NRST_JMP1.1
unnamed: D2.1 (K), FUSE_RAW1.1
unnamed: FUSE_5V1.1, LO_STAB1.OUT+, LO_STAB2.1
unnamed: I2C_C1.1, I2C_PW_SELECT1.2, I2C_U1.VCC, I2C_U2.VCC, I2C_U3.VCC
unnamed: IO_RS485.1, RS485.B-, RS485_R1.2
unnamed: IO_RS485.2, RS485.A+, RS485_R1.1
unnamed: IO_RS485.3, RS485_AUX1.2
unnamed: IO_RS485.4, RS485_AUX1.1
unnamed: RS485.RXD, RS485_J1.2
unnamed: RS485.TXD, RS485_J2.2

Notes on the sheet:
USR BUTTON
Rusty smart home, main board.
PCF8575 expander "modules": - Might have 3.3V stabilizer onboard which is not required; PCF can handle 6.5V absolute. - Have pull-ups for SDA/SCL for VCC which is NOT required and problematic. - Can handle VCC+0.5V input voltage max so 3.8V with stab. - Can't safely drive 5V "low level trigger" dev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
BOOT0!
LED!
- CAN / RS485 cables on board suggest pair-by-pair setting - not T-568B. This will distinguish cables too. But both approaches can work. - Suggested layout: Full-color for ground (on IO_CAN), Pair order: orange, green, blue, brown. IO-CAN Socket and RJ45 connector therefore: w-o o, w-g g, w-bl bl, 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
Reads switches, controls lights and other devices.
USB!
Power considerations: - 2A/5V waveshare -> 10W probably less. - relay array from ali: SRD-12VDC-SL-C x 8; 30mA single -> 0.24A @ 12V -> 2.88W - Rest of board: 0.5A @ 5V more less -> 2.5W - 10W control + 5W board & losses -> 15W - 15W -> 0.5A @30V, 0.65A @24V, 1.25A @12V, 3A @5V - 30m cable (top), c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
Board v1 ideas, maybe? - Add a pin in another axis in i2c connector for stabilization. Say - duplicated GND/VCC.
CAN uses PB8 that is also BOOT0. You need to select nBOOT_SEL to free the GPIO, otherwise the board won't boot.
Board v1 errors, to be corrected: - EVDS footprint doesn't match my device. - Battery is smaller and can be shifted right. - Can CAP can be outside. - some labels can be moved a bit away for eligibility - CAPs don't have GND marked. - Mark ground on power pins - holes of CPU could be larger - HI_ST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
OSC!
Distributed IO controller mainboard.
Design notes: - Internal pull-ups/downs are around 40kOhm which can get noisy on a long line. - FT - 5V-Tolerant; TT - 3.3V-tolerant.
Input matrix with basic protection
USART3_RX
USART3_TX

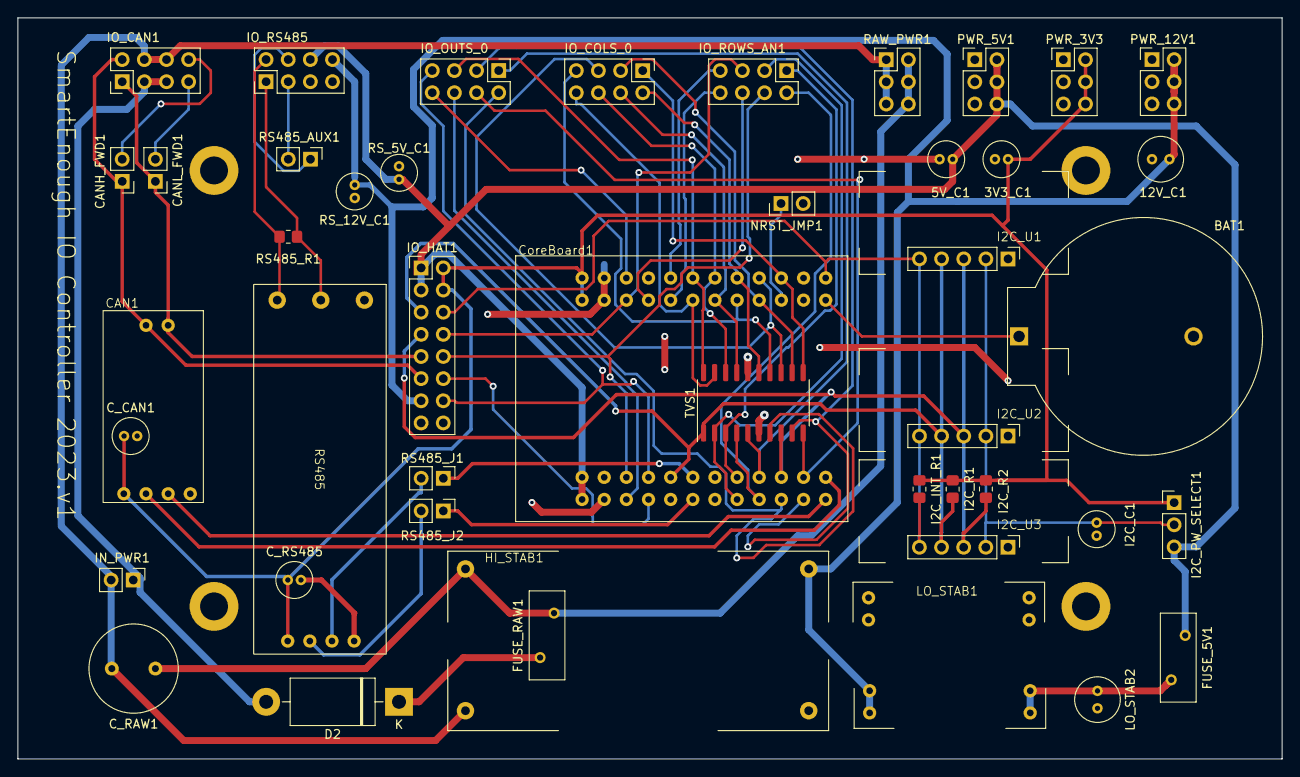
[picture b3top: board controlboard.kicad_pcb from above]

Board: 2 copper layers, 145.0 x 85.0 mm, 49 parts (0 on the bottom side), 54 nets.

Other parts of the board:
MHOLE_BL: MountingHole_3.2mm_M3_DIN965_Pad
MHOLE_RB: MountingHole_3.2mm_M3_DIN965_Pad
MHOLE_RT: MountingHole_3.2mm_M3_DIN965_Pad
MHOLE_TL: MountingHole_3.2mm_M3_DIN965_Pad

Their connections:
GND: MHOLE_BL.1, MHOLE_RB.1, MHOLE_RT.1, MHOLE_TL.1; also elsewhere on the board

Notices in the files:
hardware/power-hub/power-hub.kicad_pcb:
(c) 2025.11 by bla
hardware/uniboard-esphome/uniboard.kicad_pcb:
(c) 2025 by bla
